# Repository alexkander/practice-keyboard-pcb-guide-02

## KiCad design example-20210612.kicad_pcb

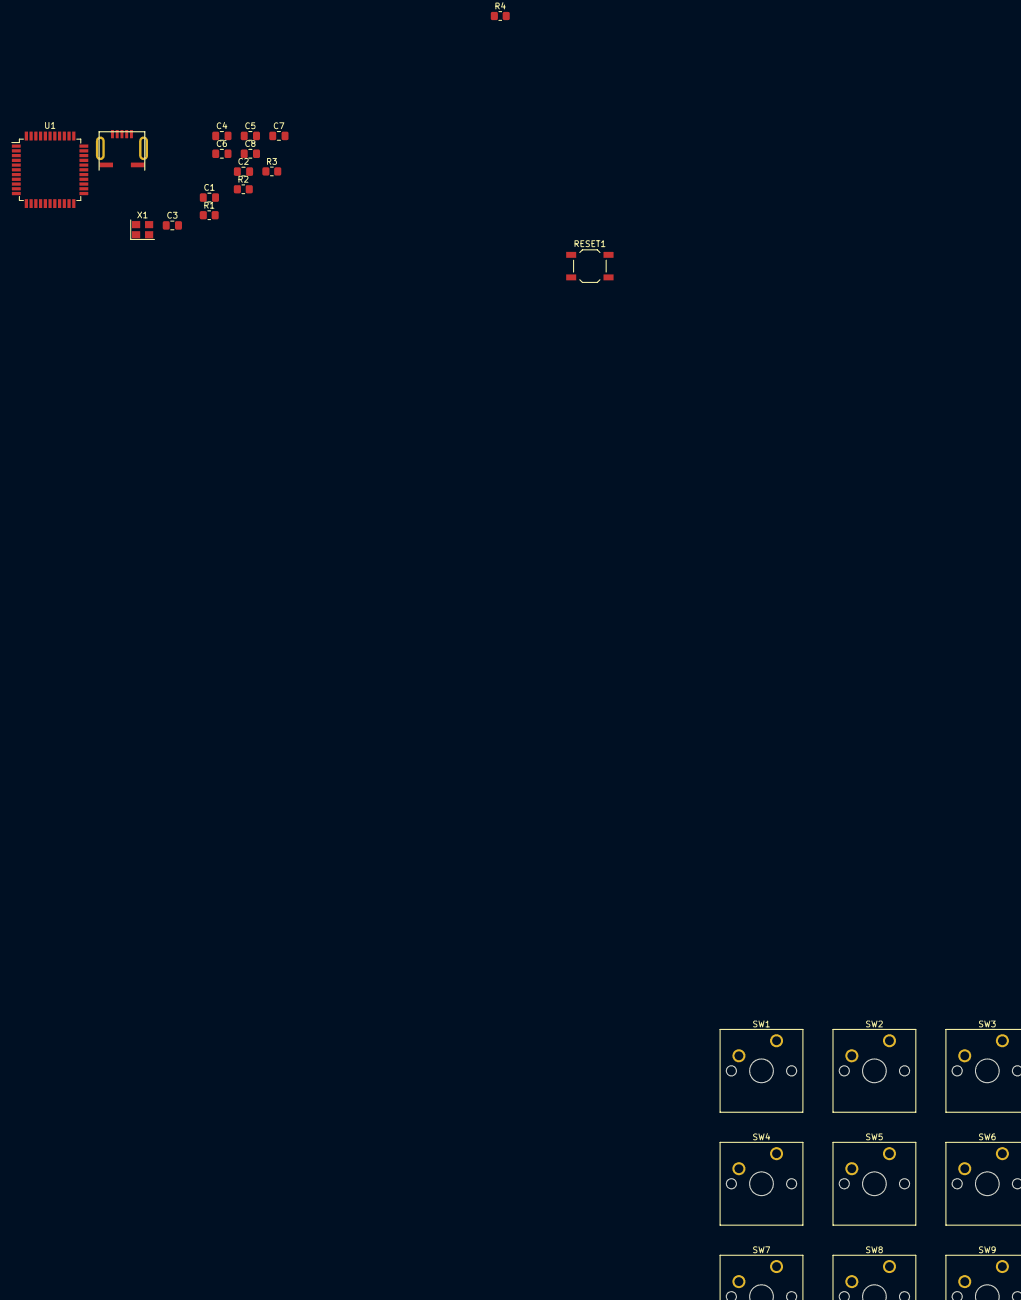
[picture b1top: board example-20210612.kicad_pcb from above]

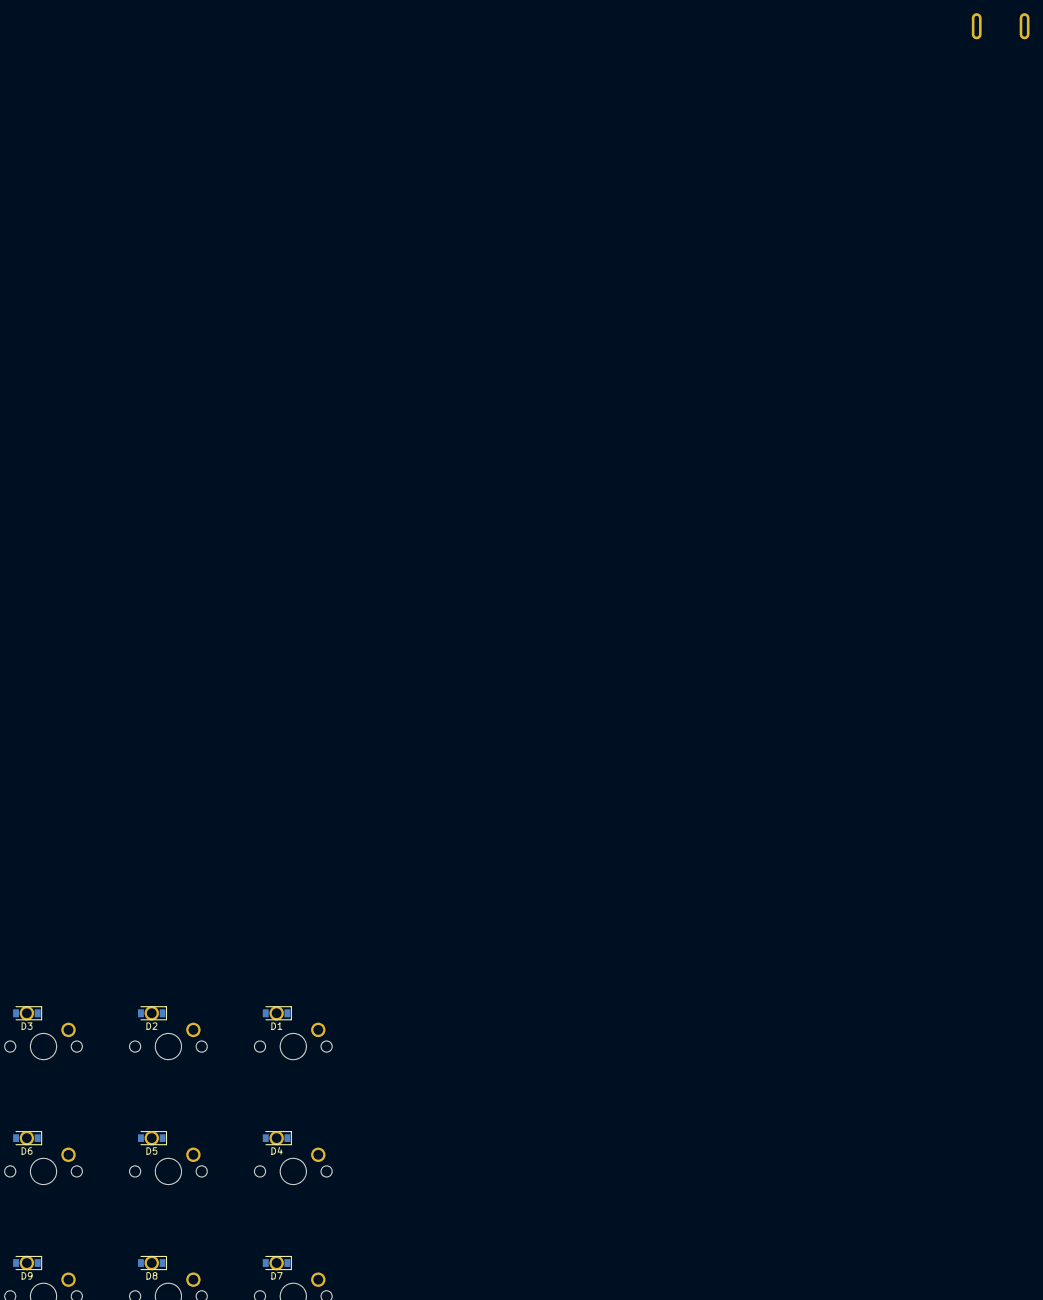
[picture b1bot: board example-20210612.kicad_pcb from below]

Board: 2 copper layers, 34 parts (9 on the bottom side), 26 nets, no tracks yet.

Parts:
C1, C2: 22p; C_0805_2012Metric_Pad1.18x1.45mm_HandSolder
C3, C4, C5, C6: 0.1u; C_0805_2012Metric_Pad1.18x1.45mm_HandSolder
C7: 4.7u; C_0805_2012Metric_Pad1.18x1.45mm_HandSolder
C8: 1u; C_0805_2012Metric_Pad1.18x1.45mm_HandSolder
D1, D2, D3, D4, D5, D6, D7, D8, D9: D; D_SOD-123
J1: USB_mini_micro_B; USB_miniB_hirose_5S8
R1, R2: 10k; R_0805_2012Metric_Pad1.20x1.40mm_HandSolder
R3, R4: 22; R_0805_2012Metric_Pad1.20x1.40mm_HandSolder
RESET1: RESET_PUSH; SW_SPST_TL3342
SW1, SW2, SW3, SW4, SW5, SW6, SW7, SW8, SW9: KEYSW; SW_Cherry_MX_1.00u_PCB
U1: ATMEGA32U4; TQFP-44_10x10mm_P0.8mm
X1: XTAL_GND; Crystal_SMD_3225-4Pin_3.2x2.5mm

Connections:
/col0: SW1.1, SW4.1, SW7.1, U1.38
/col1: SW2.1, SW5.1, SW8.1, U1.37
/col2: SW3.1, SW6.1, SW9.1, U1.36
/row0: D1.1, D2.1, D3.1, U1.41
/row1: D4.1, D5.1, D6.1, U1.40
/row2: D7.1, D8.1, D9.1, U1.39
GND: C1.2, C2.2, C3.2, C4.1, C5.1, C6.1, C7.2, C8.2, J1.5, J1.6, R2.1, RESET1.1, U1.5, U1.15, U1.23, U1.35, U1.43, X1.3
unnamed: C1.1, U1.16, X1.2
unnamed: C2.1, U1.17, X1.1
unnamed: C8.1, U1.6
unnamed: D1.2, SW1.2
unnamed: D2.2, SW2.2
unnamed: D3.2, SW3.2
unnamed: D4.2, SW4.2
unnamed: D5.2, SW5.2
unnamed: D6.2, SW6.2
unnamed: D7.2, SW7.2
unnamed: D8.2, SW8.2
unnamed: D9.2, SW9.2
unnamed: J1.2, R3.2
unnamed: J1.3, R4.2
unnamed: R1.1, RESET1.2, U1.13
unnamed: R2.2, U1.33
unnamed: R3.1, U1.3
unnamed: R4.1, U1.4
VCC: C3.1, C4.2, C5.2, C6.2, C7.1, J1.1, R1.2, U1.2, U1.7, U1.14, U1.24, U1.34, U1.44

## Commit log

2021-06-15 chore: initial commit
